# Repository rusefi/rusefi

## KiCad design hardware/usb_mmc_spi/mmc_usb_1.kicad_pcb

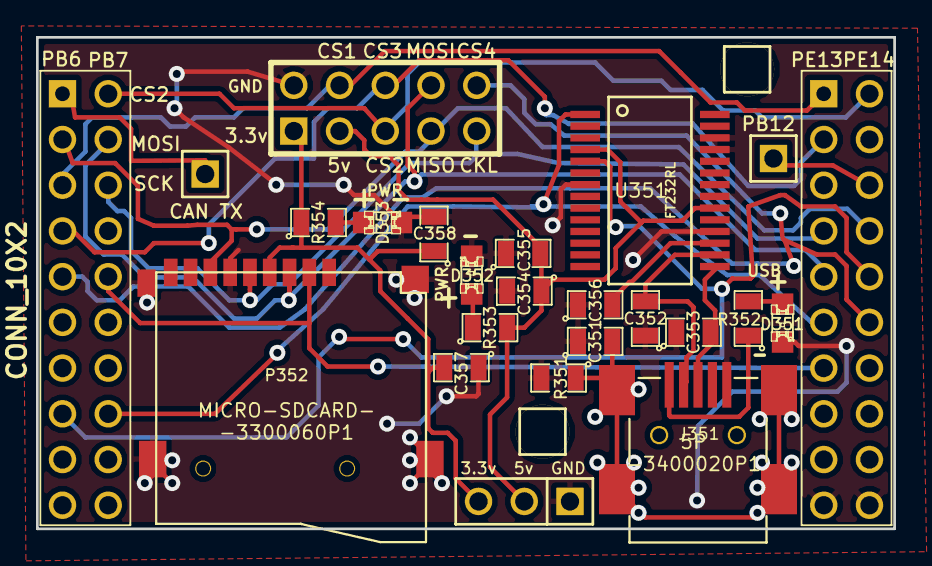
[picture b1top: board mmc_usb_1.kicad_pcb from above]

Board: 2 copper layers, 47.6 x 27.3 mm, 27 parts (1 on the bottom side), 23 nets.

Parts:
C351: 4700pF; SM0805
C352, C353: 47pF; SM0805
C354, C358: 4.7uF; SM0805
C355, C356, C357: .1uF; SM0805
D351: GREEN; LED-0805_A
D352, D353: RED; LED-0805_A
G305: LOGO; LOGO_F
J351: MINI-USB-5P-3400020P1
K351: CONN_3; PIN_ARRAY_3_A
M351, M352: CONN_1; PIN_ARRAY_1
P351: CONN_5X2; PIN_ARRAY_5x2_M
P352: MICRO-SDCARD-CONNECTOR-3300060P1
P353, P354: CONN_10X2; PIN_ARRAY_10X2_M
P355, P356: CONN_1; PIN_ARRAY_1
R351: 1M; SM0805
R352, R353, R354: 1k; SM0805
U351: FT232RL; ssop-28

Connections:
/3.3V: C357.2, C358.1, K351.3, P351.1, P352.4, R354.1
/5V: C354.1, C355.2, K351.2, P351.3, R353.2, U351.4, U351.20
/CAN_TX: P353.1, P356.1
/CS1: P351.4, P353.5, P354.1
/CS2: P351.5, P353.2, P354.2
/CS3: P351.6, P353.7, P354.3
/CS4: P351.10, P353.9, P354.12
/CS_SD_MODULE: P352.2, P353.10, P354.13
/D+: C353.2, J351.3, U351.15
/D-: C352.2, J351.2, U351.16
/SPI_MISO: P351.7, P352.7, P353.3, P354.8
/SPI_MOSI: P351.8, P352.3, P353.4, P354.9
/SPI_SCK: P351.9, P352.5, P353.6, P354.7
/USART_RX: P353.16, P354.11, U351.1
/USART_TX: P353.15, P354.10, U351.5
GND: C351.1, C352.1, C353.1, C354.2, C355.1, C356.1, C357.1, C358.2, D351.2, D352.2, D353.2, J351.5, K351.1, P351.2, P352.6, P352.G1, P352.G2, P352.G3, P352.G4, P354.19, P354.20, R351.2, U351.7, U351.18, U351.21, U351.25, U351.26
unnamed: J351.1, R352.1
unnamed: C351.2, J351.6, R351.1
unnamed: D351.1, R352.2
unnamed: D353.1, R354.2
unnamed: D352.1, R353.1
unnamed: P354.6, P355.1
unnamed: C356.2, U351.17

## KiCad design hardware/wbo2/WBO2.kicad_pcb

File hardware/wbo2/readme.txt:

Based on WBO2 1.1 from waltech.com - the source files were officially donated by Karl Walter

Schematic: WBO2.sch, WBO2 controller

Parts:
C1, C13: 10uf
C2, C7, C15: 1uf
C3: 22p
C4: 229
C5, C6: .1
C14: .1uf
D1, D2: LED
D3: DIODE-SOT
F1: FUSE
IC1: ATMEGA8-P; DIL28
K1, K2: CONN_3
L1: 10uh
P1: CONN_4
P2, P6, P7: CONN_2
Q1: MOS_N
R1: 100
R2, R9: 1.8k
R3: 18k
R4, R7, R8, R18, R19, R20, R21, R22, R23, R29: 10k
R10: 6.8k
R12: 62ohm
R13, R14: 22k
R15, R16: 12k
R17, R30: 100k
R24, R25, R26, R27, R28: 5k
U2: 7805
U4: LM324
X1: 4mhz

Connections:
/bit0: IC1.28 (PC5(ADC5/SCL)), R23.2
/bit1: IC1.27 (PC4(ADC4/SDA)), R22.2
/bit2: IC1.26 (PC3(ADC3)), R21.2
/bit3: IC1.19 (PB5(SCK)), R20.2
/bit4: IC1.18 (PB4(MISO)), R19.2
/bit5: IC1.14 (PB0(ICP)), R18.2
/nernst: IC1.25 (PC2(ADC2)), K2.1, R10.1
/pump: K2.2 (PM), R12.2, R14.2
/pump-adc: IC1.23 (PC0(ADC0)), R17.1, U4.1
/rcal: K2.3, R12.1, R13.2, U4.6 (-), U4.7
/vref: C13.2, K1.3, R1.1, R30.1
unnamed: C1.1, C6.2, D1.1 (A), IC1.7 (VCC), L1.2, P1.4, R3.1, U2.VO
unnamed: R13.1, R15.2, U4.3 (+)
unnamed: R23.1, R28.1, R29.2
unnamed: R22.1, R27.1, R28.2
unnamed: R21.1, R26.1, R27.2
unnamed: R20.1, R25.1, R26.2
unnamed: R19.1, R24.1, R25.2
unnamed: K1.1, Q1.D
unnamed: R14.1, R16.2, U4.2 (-)
unnamed: D2.1 (A), IC1.6 (PD4(XCK/T0))
unnamed: P6.1, U4.8, U4.9 (-)
unnamed: D2.2 (K), R9.2
unnamed: C14.2, R10.2
unnamed: C14.1, IC1.16 (PB2(SS/OC1B))
unnamed: IC1.15 (PB1(OC1A)), R7.2
unnamed: C2.1, IC1.21 (AREF)
unnamed: R3.2, R4.2, U4.12 (+)
unnamed: IC1.3 (PD1(TXD)), P1.3
unnamed: D1.2 (K), R2.2
unnamed: F1.1, P2.2 (PM)
unnamed: IC1.2 (PD0(RXD)), P1.2
unnamed: R1.2, U4.13 (-), U4.14
unnamed: IC1.17 (PB3(MOSI/OC2)), R8.2
unnamed: IC1.11 (PD5(T1)), Q1.G
unnamed: R15.1, R30.2
unnamed: R16.1, R17.2
unnamed: P7.2 (PM), R18.1, R24.2
unnamed: C15.2, R7.1, U4.5 (+)
unnamed: C7.2, R8.1, U4.10 (+)
unnamed: C5.1, IC1.20 (AVCC), L1.1
unnamed: C4.1, IC1.10 (PB7(XTAL2/TOSC2)), X1.2
unnamed: C3.1, IC1.9 (PB6(XTAL1/TOSC1)), X1.1
VDD: D3.3, F1.2, K1.2 (PM), U2.VI, U4.4 (VDD)
VSS: C1.2, C2.2, C3.2, C4.2, C5.2, C6.1, C7.1, C13.1, C15.1, D3.2, IC1.8 (GND), IC1.22 (AGND), P1.1, P2.1, P6.2 (PM), P7.1, Q1.S, R2.1, R4.1, R9.1, R29.1, U2.GND, U4.11 (VSS)

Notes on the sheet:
SERIAL
OUTPUT2
OUTPUT1
PUMP DRIVER
REFRENCE VOLTAGE
PUMP CURRENT MEASUREMENT
HEATER CONTROL
POWER SUPPLY

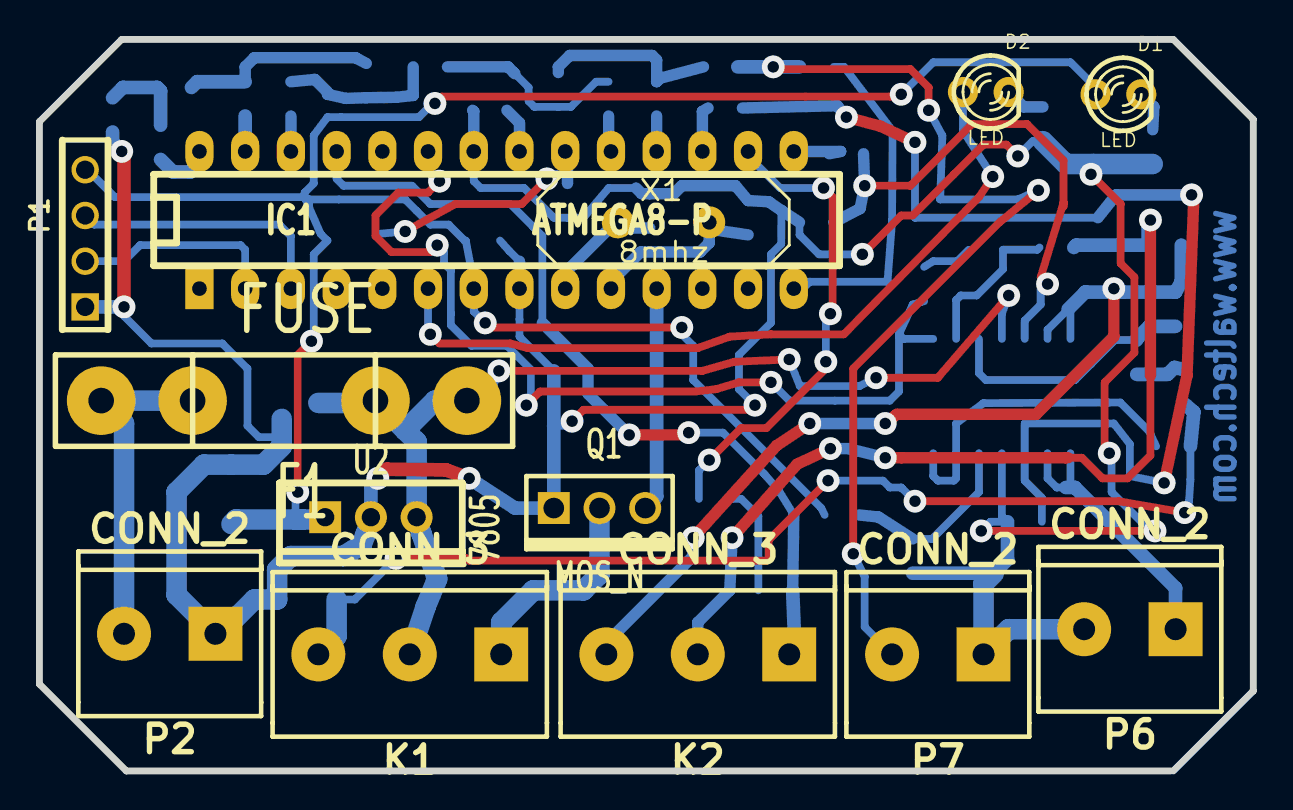
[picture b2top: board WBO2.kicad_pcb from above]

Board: 2 copper layers, 67.4 x 40.6 mm, 53 parts (0 on the bottom side), 45 nets.

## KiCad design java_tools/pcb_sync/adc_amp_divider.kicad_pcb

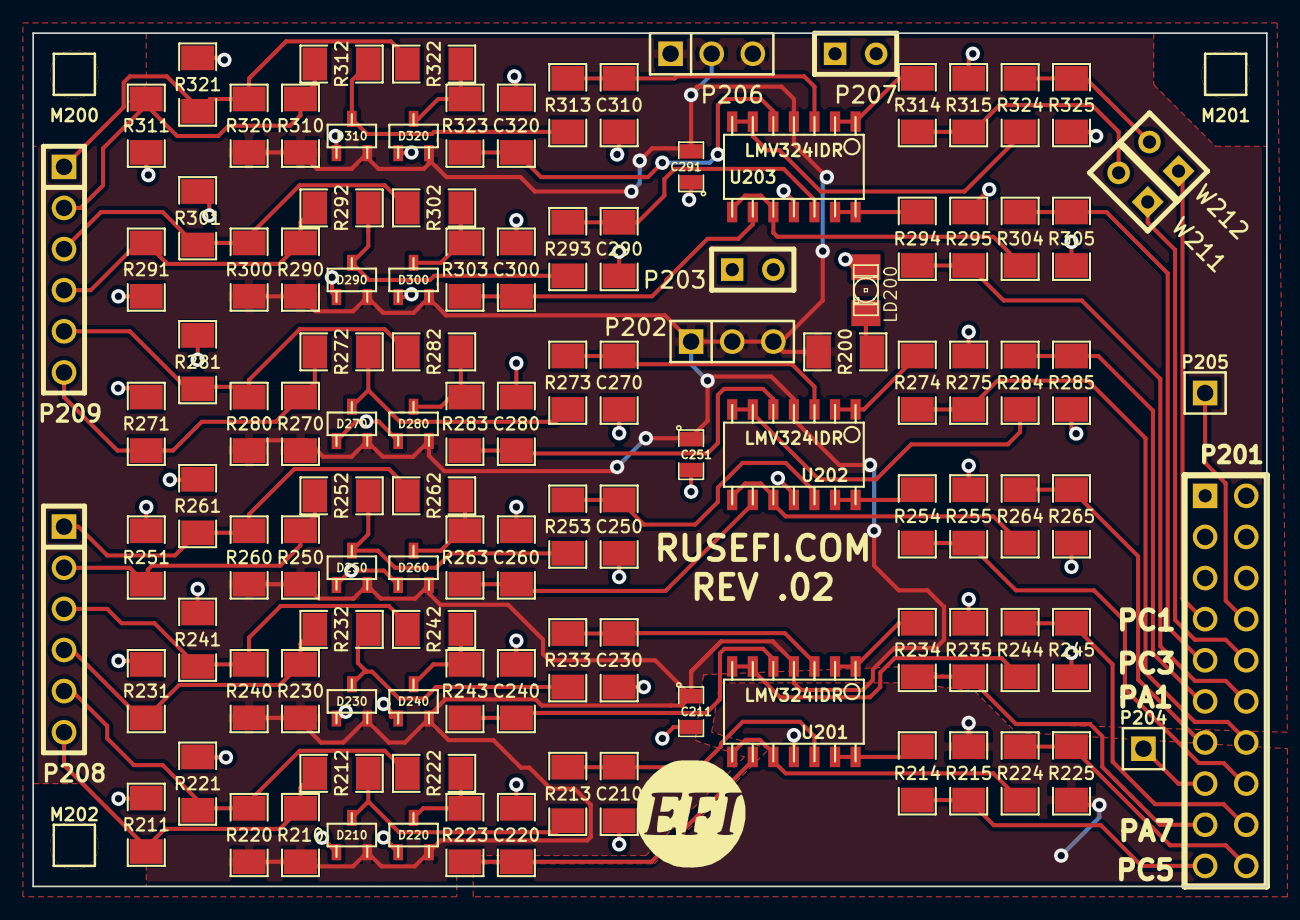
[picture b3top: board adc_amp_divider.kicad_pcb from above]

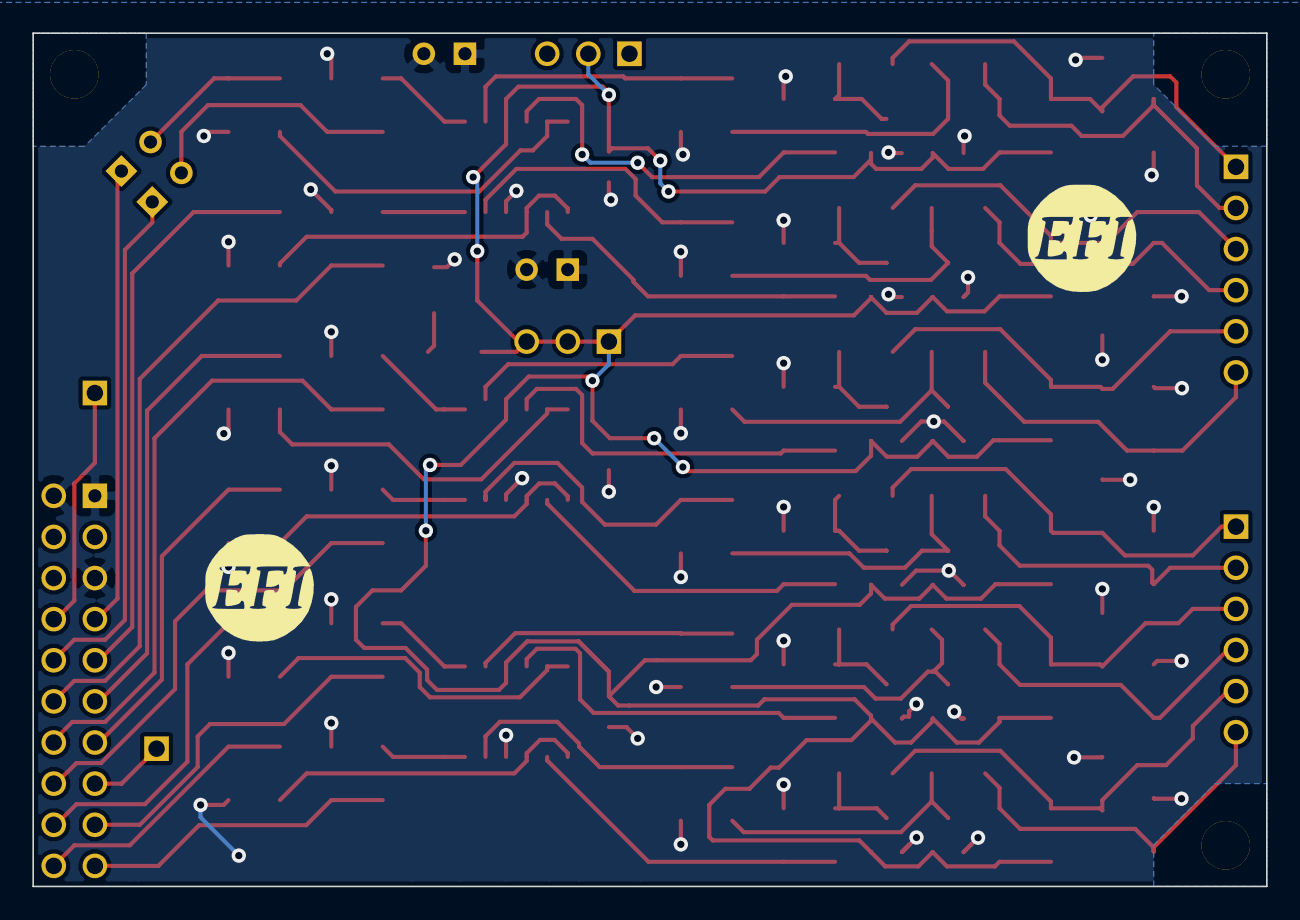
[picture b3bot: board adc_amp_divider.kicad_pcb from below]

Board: 2 copper layers, 76.2 x 52.7 mm, 121 parts (2 on the bottom side), 67 nets.

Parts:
C210, C220, C230, C240, C250, C260, C270, C280, C290, C300, C310, C320: 0.01uF; SM1206
C211, C251, C291: 0.1uF; SM0805
D210, D220, D230, D240, D250, D260, D270, D280, D290, D300, D310, D320: DOUBLE_SCHOTTKY; sot23
G200: LOGO
G201, G202: LOGO; LOGO_F
LD200: LED; LED-1206
M200, M201, M202: CONN_1; PIN_ARRAY_1
P201: CONN_10X2; PIN_ARRAY_10X2
P202, P206: CONN_3; PIN_ARRAY_3X1
P203, P207: CONN_2; SIL-2
P204, P205: CONN_1; PIN_ARRAY_1
P208, P209: CONN_6; PIN_ARRAY-6X1
R200, R213, R223, R233, R243, R253, R263, R273, R283, R293, R303, R313, R323: 100; SM1206
R210, R220, R230, R240, R250, R260, R270, R280, R290, R300, R310, R320: 2700; SM1206
R211, R221, R231, R241, R251, R261, R271, R281, R291, R301, R311, R321: 500K; SM1206
R212, R222, R232, R242, R252, R262, R272, R282, R292, R302, R312, R322: 10k; SM1206
R214, R215, R224, R225, R234, R235, R244, R245, R254, R255, R264, R265, R274, R275, R284, R285, R294, R295, R304, R305, R314, R315, R324, R325: 1500; SM1206
U201, U202, U203: LMV324IDR; so-14
W211, W212: TEST; SIL-2

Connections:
/INP1: P208.6, R210.1, R211.1, R212.1
/INP2: P208.5, R220.1, R221.1, R222.1
/INP3: P208.4, R230.1, R231.1, R232.1
/INP4: P208.3, R240.1, R241.1, R242.1
/INP5: P208.2, R250.1, R251.1, R252.1
/INP6: P208.1, R260.1, R261.1, R262.1
/INP7: P209.6, R270.1, R271.1, R272.1
/INP8: P209.5, R280.1, R281.1, R282.1
/INP9: P209.4, R290.1, R291.1, R292.1
/INP10: P209.3, R300.1, R301.1, R302.1
/INP11: P209.2, R310.1, R311.1, R312.1
/INP12: P209.1, R320.1, R321.1, R322.1
/OUT1: P201.19, R214.2, R215.1
/OUT2: P201.20, R224.2, R225.1
/OUT3: P201.17, R234.2, R235.1
/OUT4: P201.18, R244.2, R245.1
/OUT5: P201.16, R254.2, R255.1
/OUT6: P201.13, R264.2, R265.1
/OUT7: P201.14, R274.2, R275.1
/OUT8: P201.11, R284.2, R285.1
/OUT9: P201.12, R294.2, R295.1
/OUT10: P201.9, R304.2, R305.1
/OUT11: P201.10, W211.1
/OUT12: P201.7, W212.1
/PA5: P201.15, P204.1
/PC0: P201.8, P205.1
GND: C210.1, C211.2, C220.1, C230.1, C240.1, C250.1, C251.2, C260.1, C270.1, C280.1, C290.1, C291.1, C300.1, C310.1, C320.1, D210.1, D220.1, D230.1, D240.1, D250.1, D260.1, D270.1, D280.1, D290.1, D300.1, D310.1, D320.1, LD200.1, P201.1, P201.2, P201.5, P203.1, P203.2, P207.1, P207.2, R211.2, R215.2, R221.2, R225.2, R231.2, R235.2, R241.2, R245.2, R251.2, R255.2, R261.2, R265.2, R271.2, R275.2, R281.2, R285.2, R291.2, R295.2, R301.2, R305.2, R311.2, R315.2, R321.2, R325.2, U201.11, U202.11, U203.11
unnamed: D210.2, R212.2, R213.1
unnamed: D220.2, R222.2, R223.1
unnamed: C290.2, R293.2, U203.12
unnamed: C300.2, R303.2, U203.9
unnamed: D290.2, R292.2, R293.1
unnamed: D280.2, R282.2, R283.1
unnamed: D270.2, R272.2, R273.1
unnamed: D250.2, R252.2, R253.1
unnamed: D260.2, R262.2, R263.1
unnamed: D300.2, R302.2, R303.1
unnamed: R294.1, U203.13, U203.14
unnamed: R304.1, U203.8, U203.10
unnamed: C320.2, R323.2, U203.5
unnamed: D320.2, R322.2, R323.1
unnamed: D310.2, R312.2, R313.1
unnamed: R314.1, U203.1, U203.2
unnamed: C310.2, R313.2, U203.3
unnamed: R324.1, U203.6, U203.7
unnamed: R324.2, R325.1, W212.2
unnamed: R314.2, R315.1, W211.2
unnamed: R284.1, U202.6, U202.7
unnamed: R274.1, U202.1, U202.2
unnamed: R264.1, U202.8, U202.10
unnamed: R214.1, U201.13, U201.14
unnamed: R224.1, U201.8, U201.10
unnamed: R234.1, U201.1, U201.2
unnamed: R244.1, U201.6, U201.7
unnamed: C250.2, R253.2, U202.12
unnamed: R254.1, U202.13, U202.14
unnamed: C240.2, R243.2, U201.5
unnamed: D240.2, R242.2, R243.1
unnamed: C230.2, R233.2, U201.3
unnamed: C280.2, R283.2, U202.5
unnamed: C270.2, R273.2, U202.3
unnamed: C220.2, R223.2, U201.9
unnamed: C210.2, R213.2, U201.12
unnamed: C260.2, R263.2, U202.9
unnamed: LD200.2, R200.2
unnamed: D230.2, R232.2, R233.1
VCC: C211.1, C251.1, C291.2, D210.3, D220.3, D230.3, D240.3, D250.3, D260.3, D270.3, D280.3, D290.3, D300.3, D310.3, D320.3, P202.1, P202.2, P202.3, P206.1, P206.2, P206.3, R200.1, R210.2, R220.2, R230.2, R240.2, R250.2, R260.2, R270.2, R280.2, R290.2, R300.2, R310.2, R320.2, U201.4, U202.4, U203.4

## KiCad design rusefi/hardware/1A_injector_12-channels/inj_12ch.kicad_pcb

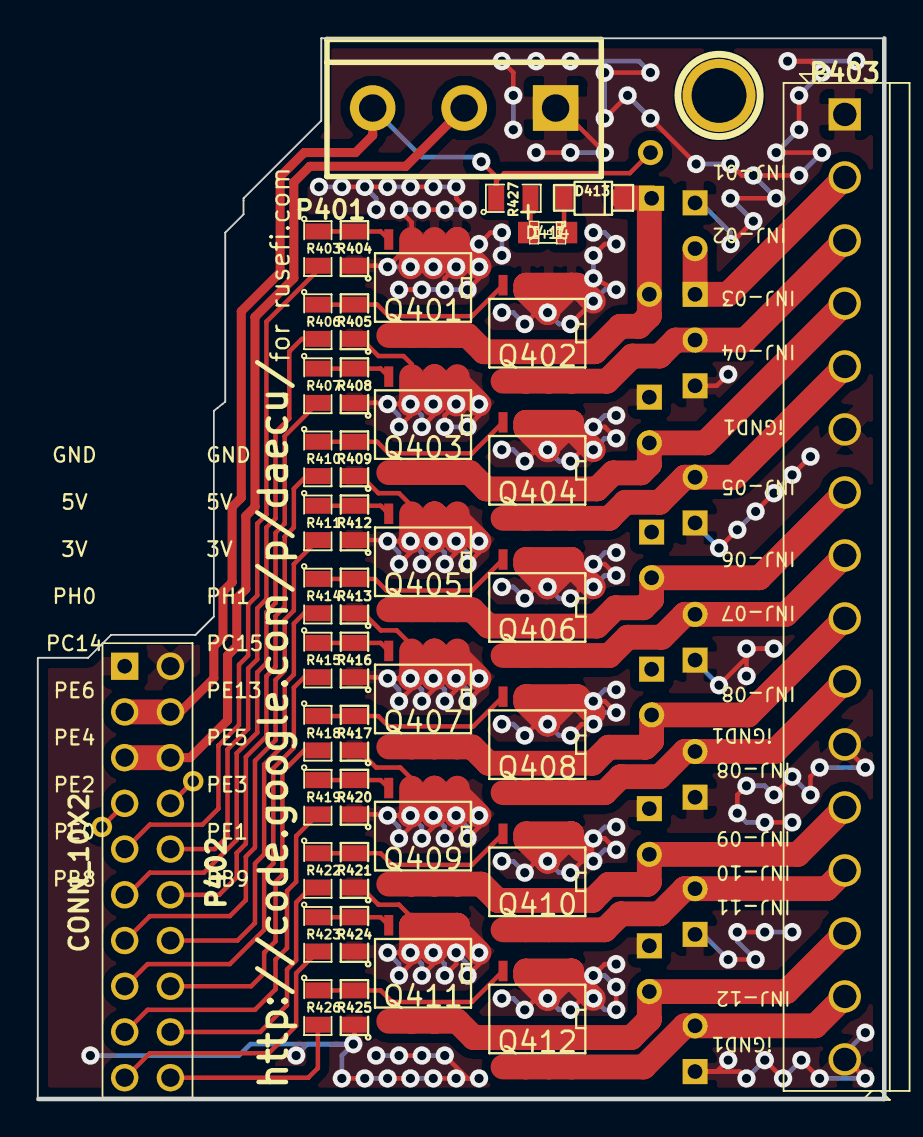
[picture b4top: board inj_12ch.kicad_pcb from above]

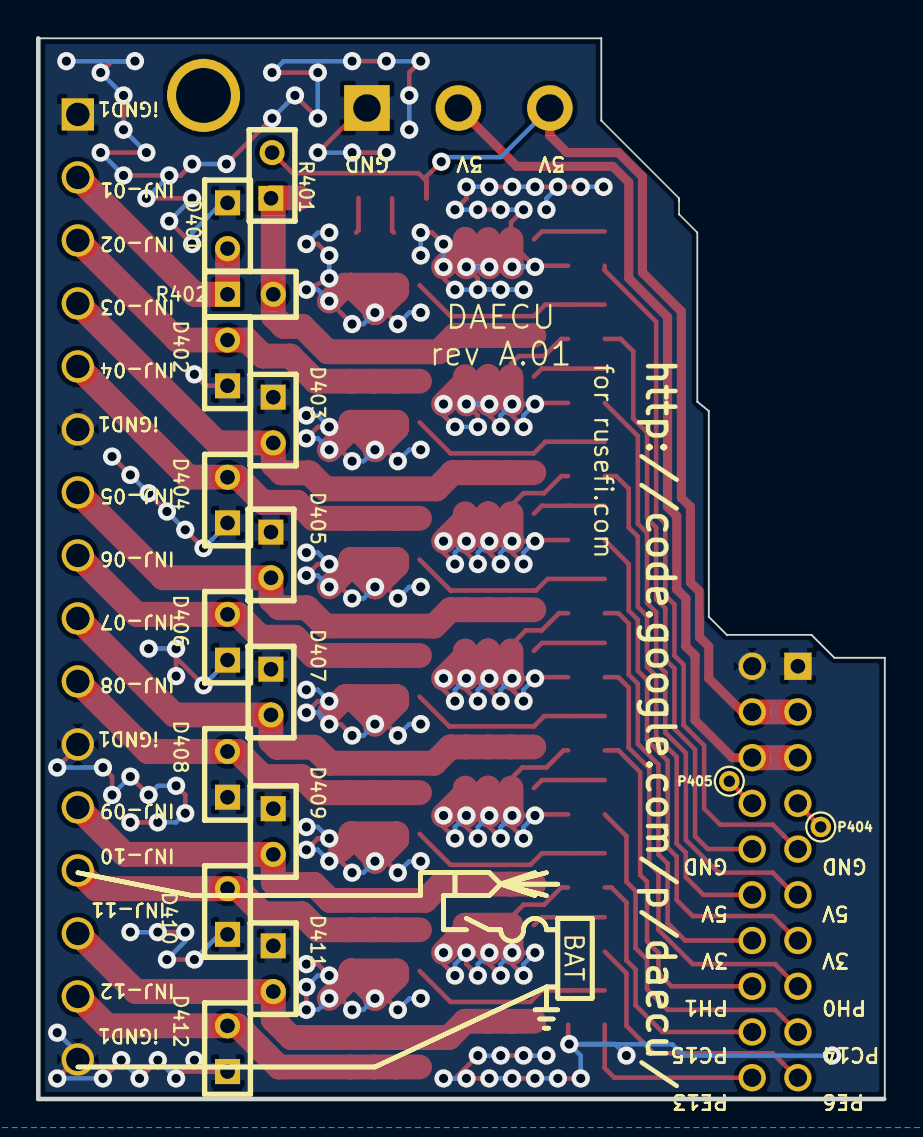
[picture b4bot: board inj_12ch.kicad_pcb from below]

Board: 2 copper layers, 47.0 x 58.9 mm, 59 parts (16 on the bottom side), 44 nets.

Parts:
D401, D402, D403, D404, D405, D406, D407, D408, D409, D410, D411, D412: DIODE; SIL-2
D413: DIODE; SOD-123
D414: LED_0805; LED-0805_A
M401: CONN_1; 1pin
P401: CONN_3; bornier3
P402: CONN_10X2; PIN_ARRAY_10X2_M
P403: CONN_16; SIL-16_3.5MM
P404, P405: CONN_1; PINTST
Q401, Q402, Q403, Q404, Q405, Q406, Q407, Q408, Q409, Q410, Q411, Q412: OVP_DRIVER; SO8E_ST
R401: OPT; SIL-2
R402: 0R; SIL-2
R403, R406, R407, R410, R411, R414, R415, R418, R419, R422, R423, R426: 20R; SM0805
R404, R405, R408, R409, R412, R413, R416, R417, R420, R421, R424, R425, R427: 1K; SM0805

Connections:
/3.3V: P401.2, P402.5, P402.6
/5V: P401.3, P402.3, P402.4, R401.2, R427.1
/INJ-01: D413.2, Q401.2, R401.1, R402.2
/INJ-01_2: D401.2, P403.2, R402.1
/INJ-01_5V: P402.9, R403.2
/INJ-02: D402.2, P403.3, Q402.2
/INJ-02_5V: P402.10, R406.2
/INJ-03: D403.2, P403.4, Q403.2
/INJ-03_5V: P402.11, R407.2
/INJ-04: D404.2, P403.5, Q404.2
/INJ-04_5V: P402.12, R410.2
/INJ-05: D405.2, P403.7, Q405.2
/INJ-05_5V: P402.13, R411.2
/INJ-06: D406.2, P403.8, Q406.2
/INJ-06_5V: P402.14, R414.2
/INJ-07: D407.2, P403.9, Q407.2
/INJ-07_5V: P402.15, R415.2
/INJ-08: D408.2, P403.10, Q408.2
/INJ-08_5V: P402.16, R418.2
/INJ-09: D409.2, P403.12, Q409.2
/INJ-09_5V: P402.17, R419.2
/INJ-10: D410.2, P403.13, Q410.2
/INJ-10_5V: P402.18, R422.2
/INJ-11: D411.2, P403.14, Q411.2
/INJ-11_5V: P402.19, R423.2
/INJ-12: D412.2, P403.15, Q412.2
/INJ-12_5V: P402.20, R426.2
/PH0: P402.7, P404.1
/PH1: P402.8, P405.1
GND: D401.1, D402.1, D403.1, D404.1, D405.1, D406.1, D407.1, D408.1, D409.1, D410.1, D411.1, D412.1, P401.1, P402.1, P402.2, P403.1, P403.6, P403.11, P403.16, Q401.3, Q402.3, Q403.3, Q404.3, Q405.3, Q406.3, Q407.3, Q408.3, Q409.3, Q410.3, Q411.3, Q412.3, R404.1, R405.1, R408.1, R409.1, R412.1, R413.1, R416.1, R417.1, R420.1, R421.1, R424.1, R425.1
unnamed: Q410.1, R421.2, R422.1
unnamed: Q408.1, R417.2, R418.1
unnamed: Q412.1, R425.2, R426.1
unnamed: D413.1, D414.2
unnamed: D414.1, R427.2
unnamed: Q404.1, R409.2, R410.1
unnamed: Q406.1, R413.2, R414.1
unnamed: Q402.1, R405.2, R406.1
unnamed: Q401.1, R403.1, R404.2
unnamed: Q405.1, R411.1, R412.2
unnamed: Q403.1, R407.1, R408.2
unnamed: Q409.1, R419.1, R420.2
unnamed: Q407.1, R415.1, R416.2
unnamed: Q411.1, R423.1, R424.2

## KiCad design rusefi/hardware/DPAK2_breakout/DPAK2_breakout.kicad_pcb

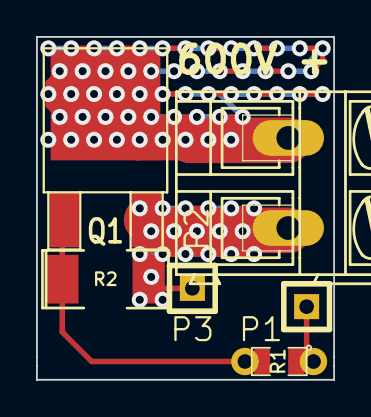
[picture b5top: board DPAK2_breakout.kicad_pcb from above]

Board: 2 copper layers, 16.5 x 19.1 mm, 6 parts (0 on the bottom side), 4 nets.

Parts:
P1, P3: CONN_1; SIL-1
P2: CONN_2; AK300-2
Q1: IRGS14C40L; DPAK2
R1: 1K; SM0805_jumper
R2: 100K; SM2010

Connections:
/GND: P2.2, P3.1, Q1.3, R2.2
/HV: P2.1, Q1.2
/SIG: P1.1, R1.1
/SIG2: Q1.1, R1.2, R2.1
